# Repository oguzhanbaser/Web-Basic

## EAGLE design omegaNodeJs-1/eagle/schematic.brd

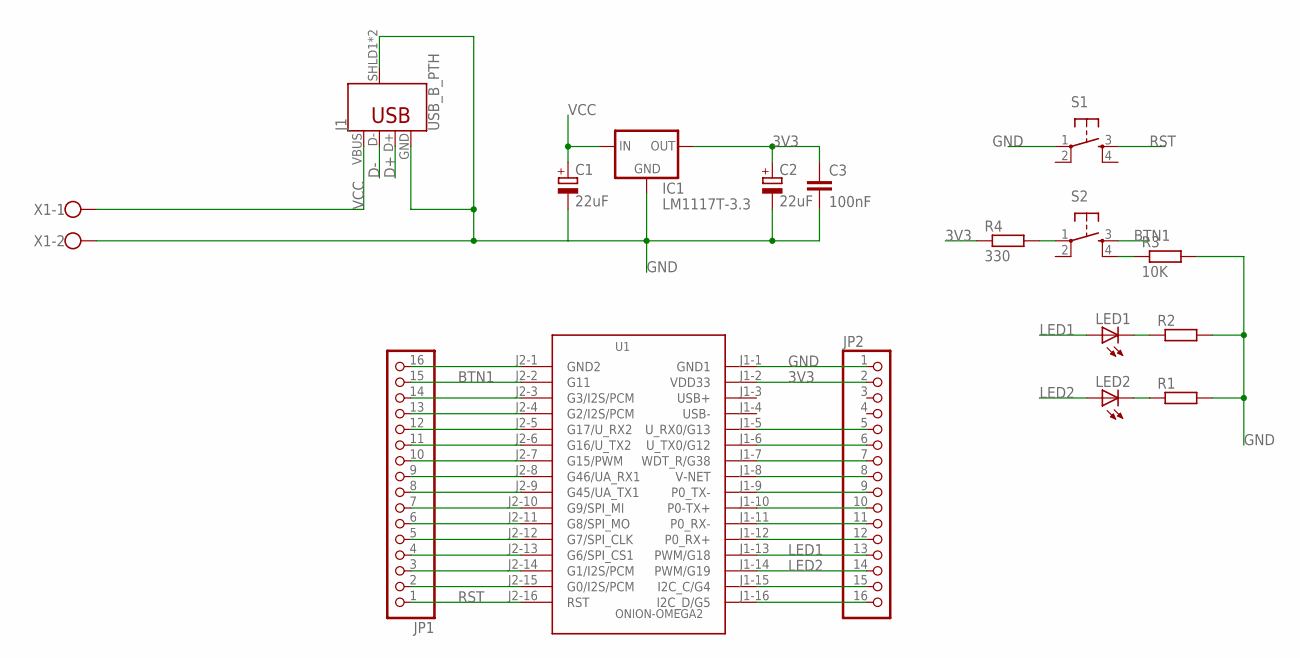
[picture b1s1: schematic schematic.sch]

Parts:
C1, C2: 22uF; E2,5-5
C3: 100nF; C050-025X075
IC1: LM1117T-3.3; TO220
J1: USB_B_PTH; USB-B-PTH
JP1, JP2: PINHD-1X16; 1X16
LED1, LED2: LED5MM
R1, R2: R-EU_0204/7; 0204/7
R3: 10K; 0204/7
R4: 330; 0204/7
S1, S2: TAC_SWITCHPTH; TACTILE-PTH
U1: ONION-OMEGA2; ONION-2MM-2X16
X1: W237-102

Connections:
3V3: C2.+, C3.1, IC1.2 (OUT), JP2.2, R4.1, U1.J1-2 (VDD33)
BTN1: JP1.15, S2.3, U1.J2-2 (G11)
D+: J1.D+
D-: J1.D-
GND: C1.-, C2.-, C3.2, IC1.1 (GND), J1.GND, J1.SHLD1 (SHIELD), J1.SHLD2 (SHIELD), JP2.1, R1.2, R2.2, R3.2, S1.1, U1.J1-1 (GND1), X1.2
LED1: JP2.13, LED1.A, U1.J1-13 (PWM/G18)
LED2: JP2.14, LED2.A, U1.J1-14 (PWM/G19)
unnamed: JP1.16, U1.J2-1 (GND2)
unnamed: JP1.14, U1.J2-3 (G3/I2S/PCM)
unnamed: JP1.13, U1.J2-4 (G2/I2S/PCM)
unnamed: JP1.12, U1.J2-5 (G17/U_RX2)
unnamed: JP1.11, U1.J2-6 (G16/U_TX2)
unnamed: JP1.10, U1.J2-7 (G15/PWM)
unnamed: JP1.9, U1.J2-8 (G46/UA_RX1)
unnamed: JP1.8, U1.J2-9 (G45/UA_TX1)
unnamed: JP1.7, U1.J2-10 (G9/SPI_MI)
unnamed: JP1.6, U1.J2-11 (G8/SPI_MO)
unnamed: JP1.5, U1.J2-12 (G7/SPI_CLK)
unnamed: JP1.4, U1.J2-13 (G6/SPI_CS1)
unnamed: JP1.3, U1.J2-14 (G1/I2S/PCM)
unnamed: JP1.2, U1.J2-15 (G0/I2S/PCM)
unnamed: LED1.K (C), R2.1
unnamed: LED2.K (C), R1.1
unnamed: R3.1, S2.4
unnamed: R4.2, S2.1
unnamed: JP2.5, U1.J1-5 (U_RX0/G13)
unnamed: JP2.6, U1.J1-6 (U_TX0/G12)
unnamed: JP2.7, U1.J1-7 (WDT_R/G38)
unnamed: JP2.8, U1.J1-8 (V-NET)
unnamed: JP2.9, U1.J1-9 (P0_TX-)
unnamed: JP2.10, U1.J1-10 (P0-TX+)
unnamed: JP2.11, U1.J1-11 (P0_RX-)
unnamed: JP2.12, U1.J1-12 (P0_RX+)
unnamed: JP2.15, U1.J1-15 (I2C_C/G4)
unnamed: JP2.16, U1.J1-16 (I2C_D/G5)
RST: JP1.1, S1.3, U1.J2-16 (RST)
VCC: C1.+, IC1.3 (IN), J1.VBUS, X1.1

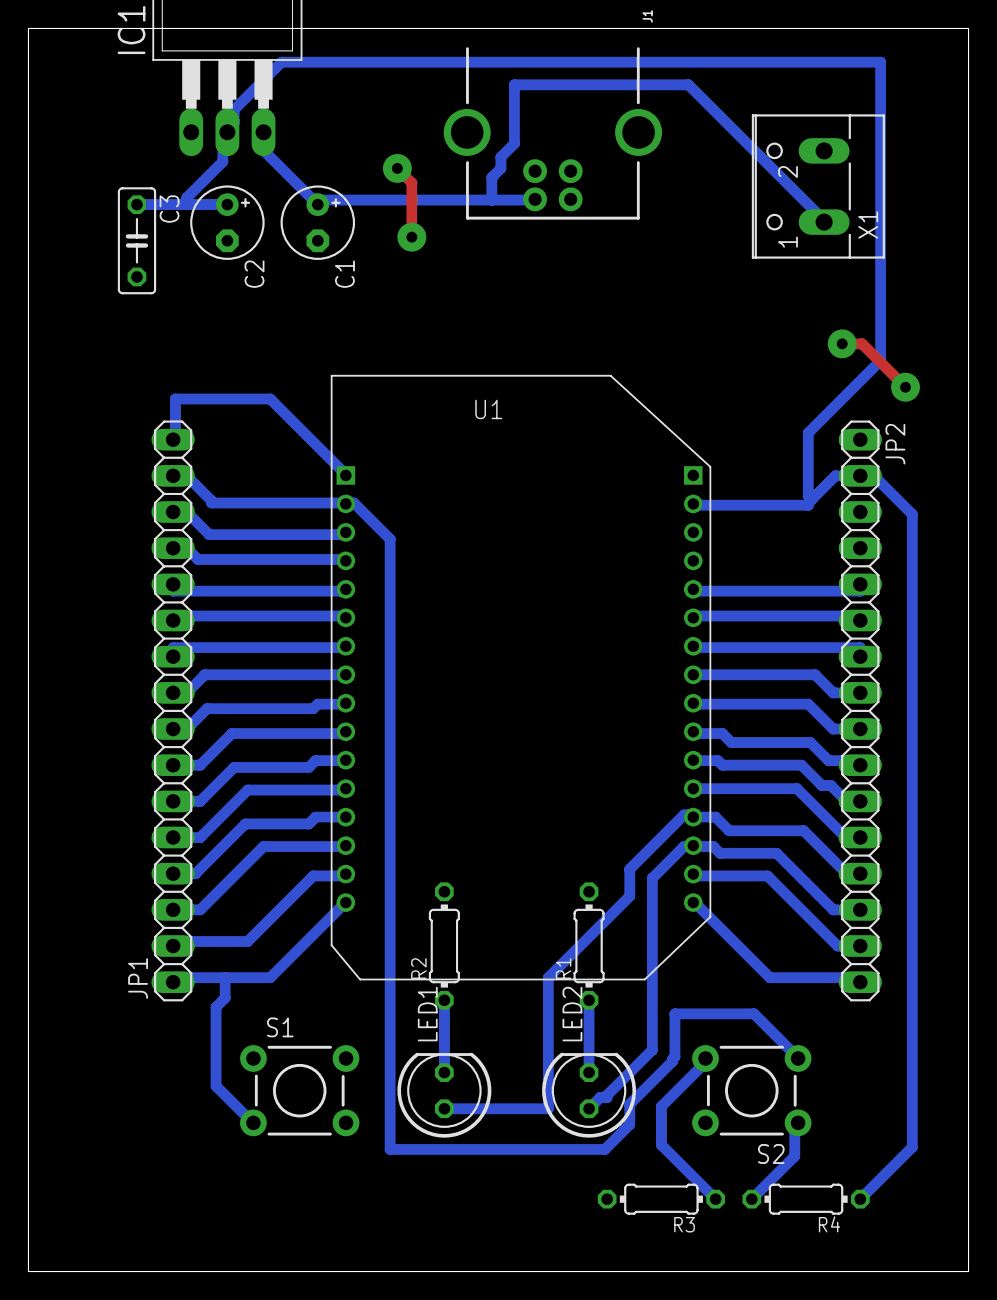
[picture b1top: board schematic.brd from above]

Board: 2 copper layers, 66.0 x 87.3 mm, 17 parts (0 on the bottom side), 35 nets.

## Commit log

2016-05-21 Create gh-pages branch via GitHub
2017-05-05 tcp client example
2017-05-05 tcp client example v1.1
2017-11-04 omega 2
2017-11-04 eagle
2018-04-28 mqtt
2018-06-13 mongoose
2018-06-14 edit
2018-06-14 link edit

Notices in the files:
parts and their libraries:
SparkFun-Retired: Licensing: Creative Commons ShareAlike 4.0 International - https://creativecommons.org/licenses/by-sa/4.0
